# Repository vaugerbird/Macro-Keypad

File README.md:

# Macro-Keypad
Designed by vaugerbird

Features
---------

* Features 6 programable macro keys
* Controlled by ATMega32u4 that can be flashed with Arduino bootloader
* Uses a USB Type C connector at USB 2.0 speeds
* Updated Pro Micro board is also included (great for beginners)

Notes
------

All of the mechanical key switches are all programed in EAGLE as Cherry MX keys or equivalent footprint

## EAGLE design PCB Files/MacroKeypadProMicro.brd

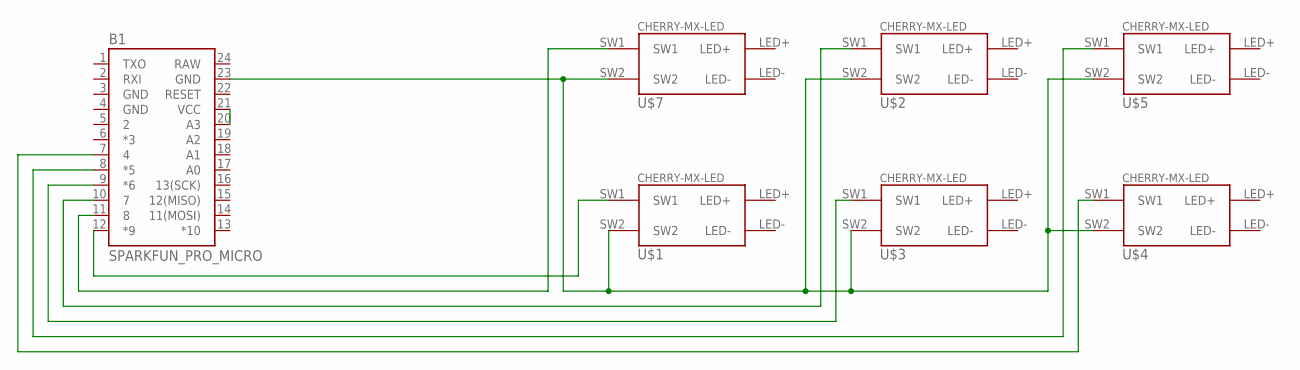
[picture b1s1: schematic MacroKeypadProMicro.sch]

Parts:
B1: SPARKFUN_PRO_MICRO
U$1, U$2, U$3, U$4, U$5, U$7: CHERRY-MX-LED

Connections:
GND: B1.3 (GND), B1.4 (GND), B1.23 (GND), U$1.SW2, U$2.SW2, U$3.SW2, U$4.SW2, U$5.SW2, U$7.SW2
unnamed: B1.20 (A3), B1.21 (VCC)
RAW: B1.24 (RAW)
SW1: B1.11 (8), U$7.SW1
SW2: B1.9 (*6), U$3.SW1
SW3: B1.7 (4), U$4.SW1
SW4: B1.12 (*9), U$1.SW1
SW5: B1.10 (7), U$2.SW1
SW6: B1.8 (*5), U$5.SW1

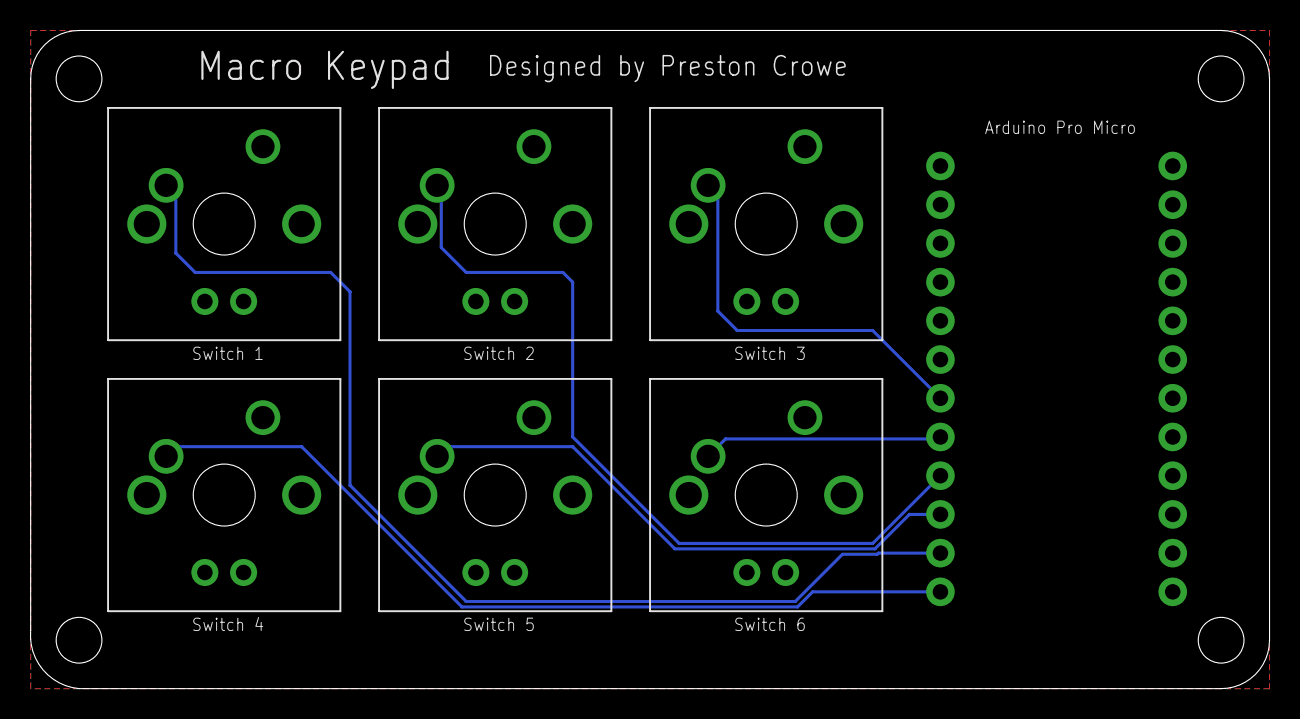
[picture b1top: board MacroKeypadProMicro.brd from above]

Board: 2 copper layers, 81.3 x 43.2 mm, 7 parts (0 on the bottom side), 8 nets.

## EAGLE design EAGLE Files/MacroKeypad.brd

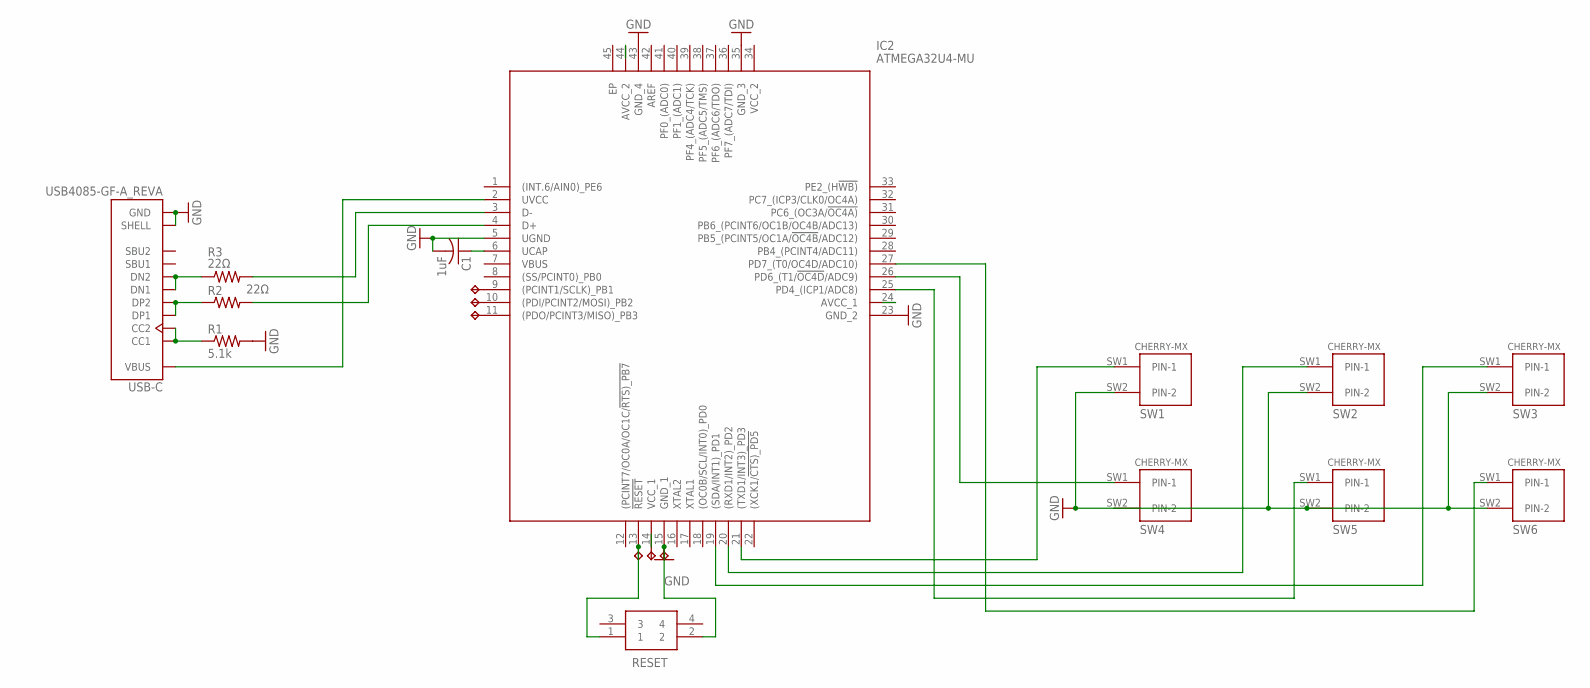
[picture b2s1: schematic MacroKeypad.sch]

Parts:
5V: TPTP17R; TP17R
C1: 1uF; C0805
GND: TPTP17R; TP17R
IC2: ATMEGA32U4-MU; QFN50P700X700X100-45N
MISO: TPTP17R; TP17R
MOSI: TPTP17R; TP17R
R1: 5.1k; R0603
R2, R3: 22Ω; R0805
RESET: LL3303F065QG
RST: TPTP17R; TP17R
SCLK: TPTP17R; TP17R
SW1, SW2, SW3, SW4, SW5, SW6: CHERRY-MX
USB-C: USB4085-GF-A_REVA; GCT_USB4085-GF-A_REVA

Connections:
CC: R1.1, USB-C.A5 (CC1), USB-C.B5 (CC2)
D+: R2.1, USB-C.A6 (DP1), USB-C.B6 (DP2)
D+RES: IC2.4 (D+), R2.2
D-: R3.1, USB-C.A7 (DN1), USB-C.B7 (DN2)
D-RES: IC2.3 (D-), R3.2
GND: C1.2, GND.TP, IC2.5 (UGND), IC2.15 (GND_1), IC2.23 (GND_2), IC2.35 (GND_3), IC2.43 (GND_4), R1.2, RESET.2, SW1.SW2 (PIN-2), SW2.SW2 (PIN-2), SW3.SW2 (PIN-2), SW4.SW2 (PIN-2), SW5.SW2 (PIN-2), SW6.SW2 (PIN-2), USB-C.A1 (GND), USB-C.A12 (GND), USB-C.B1 (GND), USB-C.B12 (GND), USB-C.P1 (SHELL), USB-C.P2 (SHELL), USB-C.P3 (SHELL), USB-C.P4 (SHELL)
MISO: IC2.11 ((PDO/PCINT3/MISO)_PB3), MISO.TP
MOSI: IC2.10 ((PDI/PCINT2/MOSI)_PB2), MOSI.TP
RESET: IC2.13 (!RESET), RESET.1, RST.TP
SCLK: IC2.9 ((PCINT1/SCLK)_PB1), SCLK.TP
SW1: IC2.21 ((TXD1/INT3)_PD3), SW1.SW1 (PIN-1)
SW2: IC2.20 ((RXD1/INT2)_PD2), SW2.SW1 (PIN-1)
SW3: IC2.19 ((SDA/INT1)_PD1), SW3.SW1 (PIN-1)
SW4: IC2.26 (PD6_(T1/!OC4D!/ADC9)), SW4.SW1 (PIN-1)
SW5: IC2.25 (PD4_(ICP1/ADC8)), SW5.SW1 (PIN-1)
SW6: IC2.27 (PD7_(T0/OC4D/ADC10)), SW6.SW1 (PIN-1)
UCAP: C1.1, IC2.6 (UCAP)
VCC: 5V.TP, IC2.14 (VCC_1), IC2.24 (AVCC_1), IC2.44 (AVCC_2)
VIN: IC2.2 (UVCC), USB-C.A4 (VBUS), USB-C.A9 (VBUS), USB-C.B4 (VBUS), USB-C.B9 (VBUS)

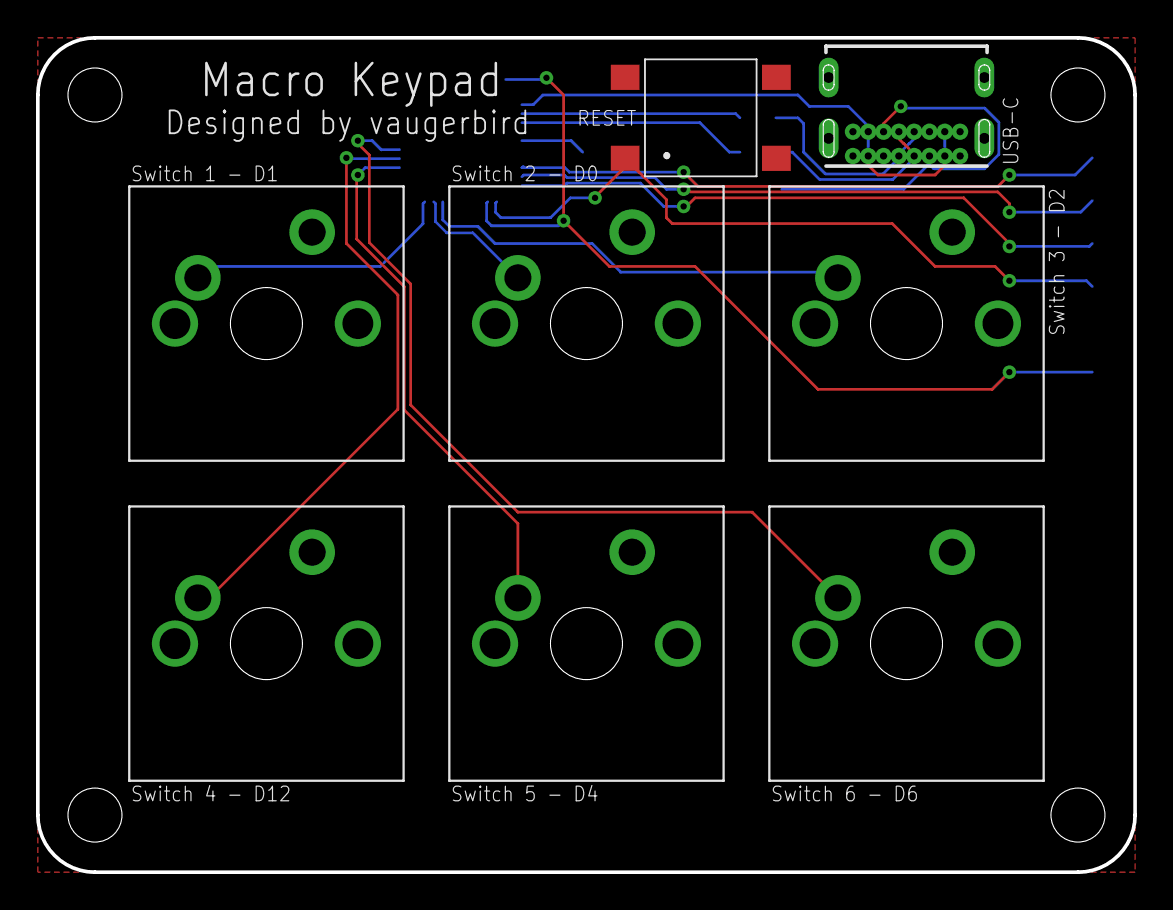
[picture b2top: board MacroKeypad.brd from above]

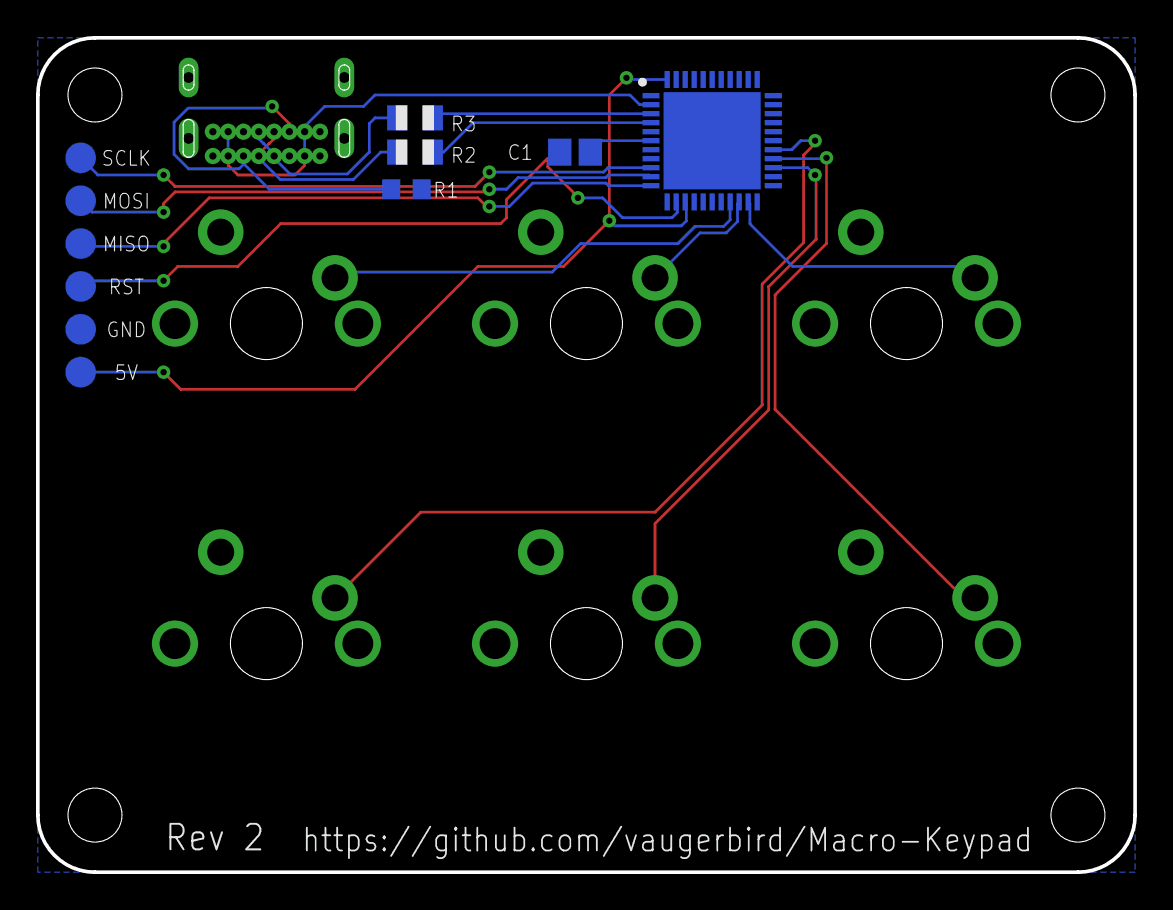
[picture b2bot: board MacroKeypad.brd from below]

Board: 2 copper layers, 61.0 x 46.4 mm, 19 parts (11 on the bottom side), 19 nets.

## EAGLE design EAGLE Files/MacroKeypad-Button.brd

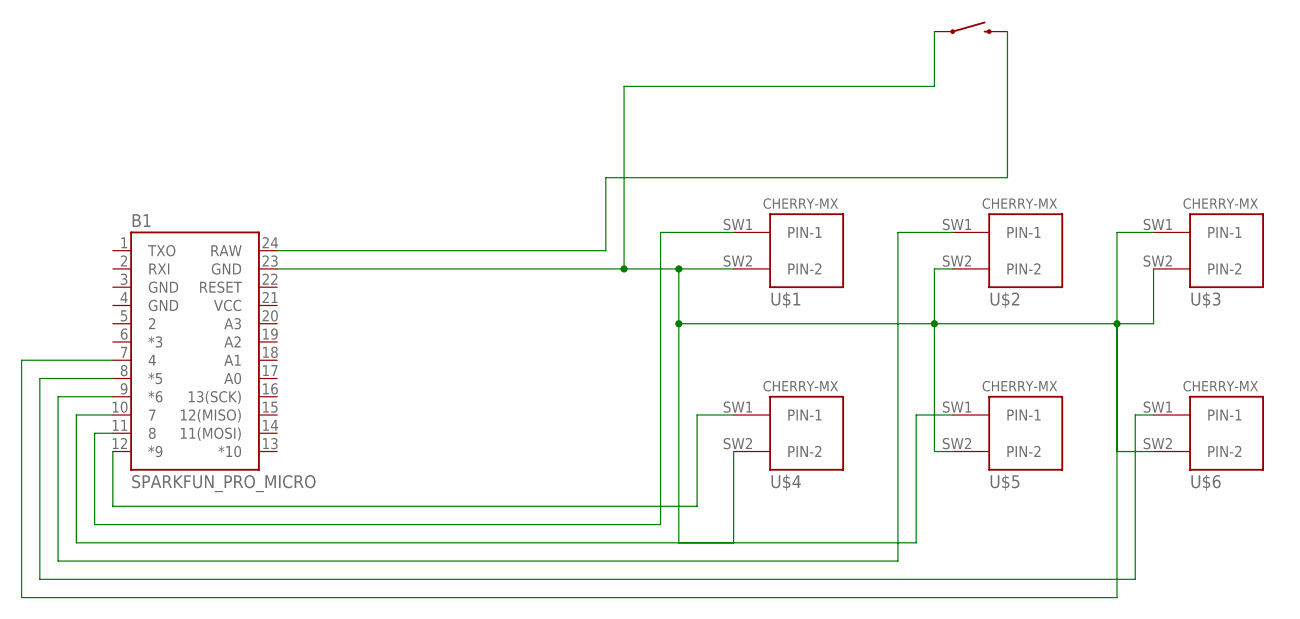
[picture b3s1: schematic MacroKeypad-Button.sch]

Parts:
B1: SPARKFUN_PRO_MICRO
S1: MOMENTARY-SWITCH-SPST-PTH-6.0MM; TACTILE_SWITCH_PTH_6.0MM
U$1, U$2, U$3, U$4, U$5, U$6: CHERRY-MX

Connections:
GND: B1.3 (GND), B1.4 (GND), B1.23 (GND), S1.1, U$1.SW2 (PIN-2), U$2.SW2 (PIN-2), U$3.SW2 (PIN-2), U$4.SW2 (PIN-2), U$5.SW2 (PIN-2), U$6.SW2 (PIN-2)
RESET: B1.24 (RAW), S1.3 (2)
SW1: B1.11 (8), U$1.SW1 (PIN-1)
SW2: B1.9 (*6), U$2.SW1 (PIN-1)
SW3: B1.7 (4), U$3.SW1 (PIN-1)
SW4: B1.12 (*9), U$4.SW1 (PIN-1)
SW5: B1.10 (7), U$5.SW1 (PIN-1)
SW6: B1.8 (*5), U$6.SW1 (PIN-1)
VCC: B1.21 (VCC)

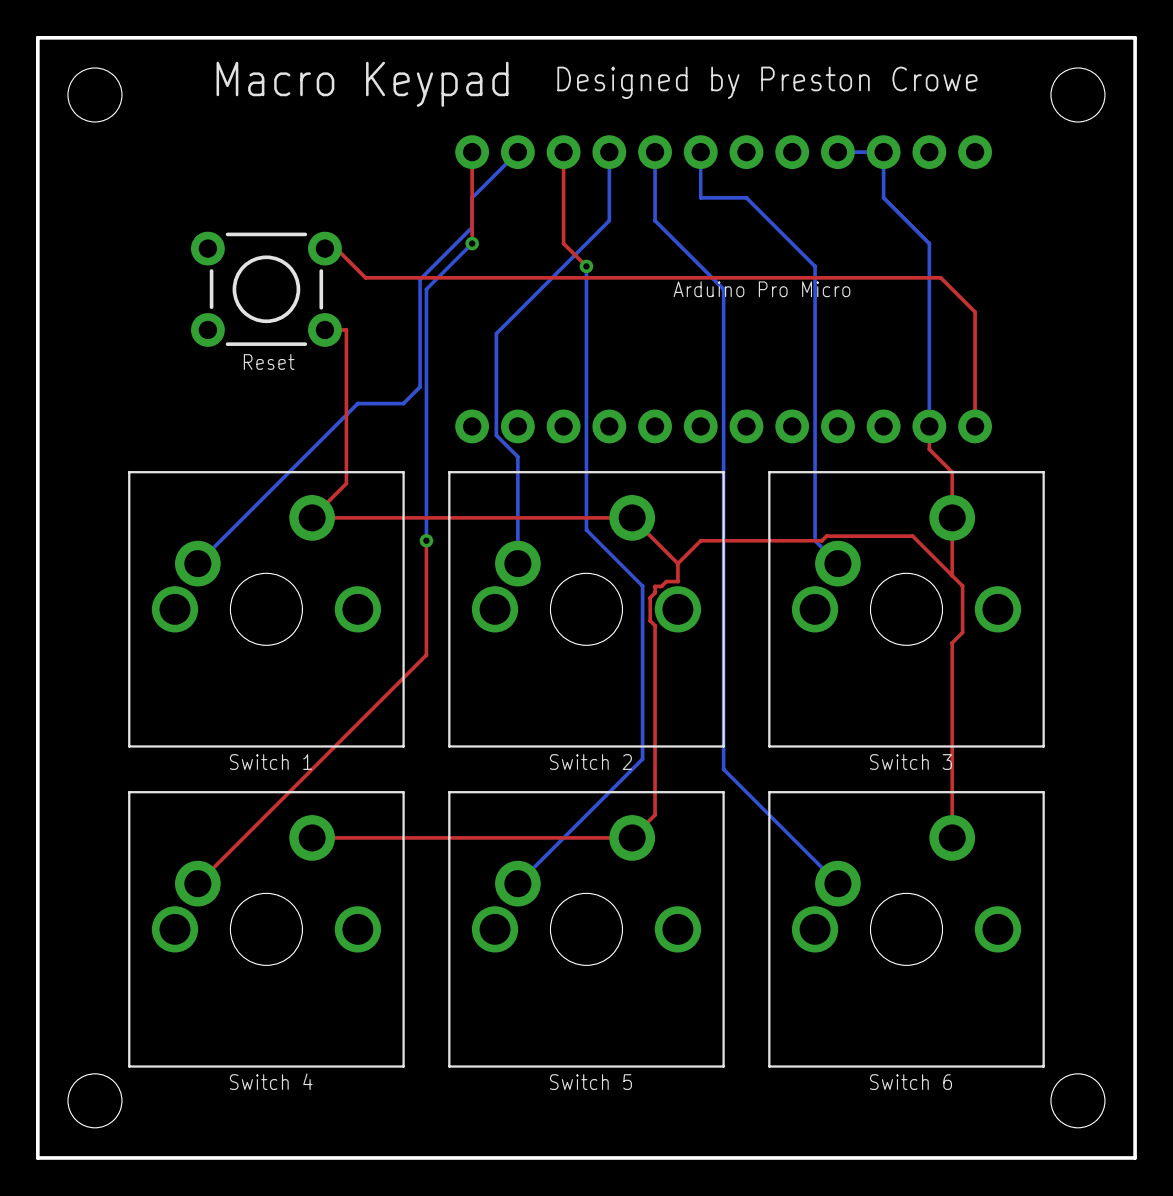
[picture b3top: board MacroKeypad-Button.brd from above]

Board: 2 copper layers, 61.0 x 62.2 mm, 8 parts (0 on the bottom side), 8 nets.

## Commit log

2019-02-19 Re-added files w/ corrected files
2020-11-25 Clean up old files
2020-11-26 Brand new PCB started
    Started redesigning PCB and added BOM
2020-11-26 Update more files
2020-11-26 Update with new LICENCE
2020-11-26 (Almost) Finished with the redo
    Pretty much done, just need to fix USB-C port footprint and make code for the new board
2020-11-26 Create LICENSE
2020-11-26 Update README.md
    Hopefully the last one for a bit
2020-11-26 Add BOM
    I deleted it before previous push
2020-11-27 Add programming pads
    Also added the BOM as it was missing
2020-11-27 Fix switch 6 and add switch pinout
2020-11-29 Update MacroKeypad.brd
    Had to change a DRC setting to fix the USB C port. Read up here for more info: https://support.snapeda.com/en/articles/3533844-why-do-pads-overlap-when-adding-to-board-design
2020-11-29 Prep for pull
2020-11-29 Add Gerber files for new PCB
2020-11-29 Rename file
2021-03-10 Finished updated Pro Micro board

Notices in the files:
parts and their libraries:
SparkFun-Boards: Licensing: Creative Commons ShareAlike 4.0 International - https://creativecommons.org/licenses/by-sa/4.0
